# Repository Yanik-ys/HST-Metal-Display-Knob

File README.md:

# HST-Metal-Display-Knob
This repo is for the school project Metal-Display-Knob

The project is based on the project [smartknob](https://github.com/scottbez1/smartknob?tab=readme-ov-file) from [scottbez1](https://github.com/scottbez1)

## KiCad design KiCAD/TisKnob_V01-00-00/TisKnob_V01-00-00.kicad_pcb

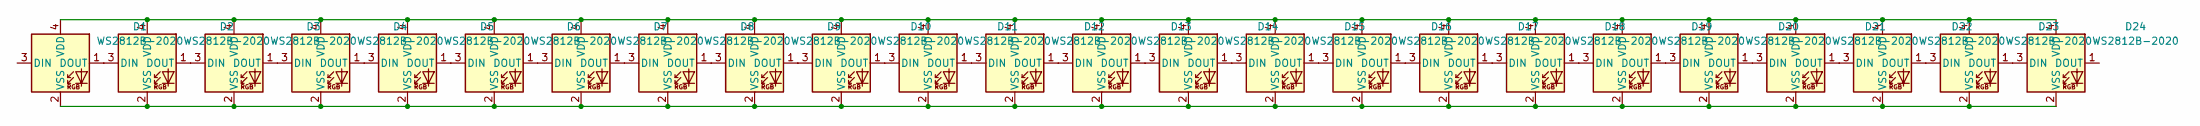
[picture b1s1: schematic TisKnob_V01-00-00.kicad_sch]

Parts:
D1, D2, D3, D4, D5, D6, D7, D8, D9, D10, D11, D12, D13, D14, D15, D16, D17, D18, D19, D20, D21, D22, D23, D24: WS2812B-2020; LED_WS2812B-2020_PLCC4_2.0x2.0mm

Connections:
unnamed: D1.1 (DOUT), D2.3 (DIN)
unnamed: D1.4 (VDD), D2.4 (VDD), D3.4 (VDD), D4.4 (VDD), D5.4 (VDD), D6.4 (VDD), D7.4 (VDD), D8.4 (VDD), D9.4 (VDD), D10.4 (VDD), D11.4 (VDD), D12.4 (VDD), D13.4 (VDD), D14.4 (VDD), D15.4 (VDD), D16.4 (VDD), D17.4 (VDD), D18.4 (VDD), D19.4 (VDD), D20.4 (VDD), D21.4 (VDD), D22.4 (VDD), D23.4 (VDD), D24.4 (VDD)
unnamed: D1.2 (VSS), D2.2 (VSS), D3.2 (VSS), D4.2 (VSS), D5.2 (VSS), D6.2 (VSS), D7.2 (VSS), D8.2 (VSS), D9.2 (VSS), D10.2 (VSS), D11.2 (VSS), D12.2 (VSS), D13.2 (VSS), D14.2 (VSS), D15.2 (VSS), D16.2 (VSS), D17.2 (VSS), D18.2 (VSS), D19.2 (VSS), D20.2 (VSS), D21.2 (VSS), D22.2 (VSS), D23.2 (VSS), D24.2 (VSS)
unnamed: D2.1 (DOUT), D3.3 (DIN)
unnamed: D3.1 (DOUT), D4.3 (DIN)
unnamed: D4.1 (DOUT), D5.3 (DIN)
unnamed: D5.1 (DOUT), D6.3 (DIN)
unnamed: D6.1 (DOUT), D7.3 (DIN)
unnamed: D7.1 (DOUT), D8.3 (DIN)
unnamed: D8.1 (DOUT), D9.3 (DIN)
unnamed: D9.1 (DOUT), D10.3 (DIN)
unnamed: D10.1 (DOUT), D11.3 (DIN)
unnamed: D11.1 (DOUT), D12.3 (DIN)
unnamed: D12.1 (DOUT), D13.3 (DIN)
unnamed: D13.1 (DOUT), D14.3 (DIN)
unnamed: D14.1 (DOUT), D15.3 (DIN)
unnamed: D15.1 (DOUT), D16.3 (DIN)
unnamed: D16.1 (DOUT), D17.3 (DIN)
unnamed: D17.1 (DOUT), D18.3 (DIN)
unnamed: D18.1 (DOUT), D19.3 (DIN)
unnamed: D19.1 (DOUT), D20.3 (DIN)
unnamed: D20.1 (DOUT), D21.3 (DIN)
unnamed: D21.1 (DOUT), D22.3 (DIN)
unnamed: D22.1 (DOUT), D23.3 (DIN)
unnamed: D23.1 (DOUT), D24.3 (DIN)

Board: 2 copper layers, 24 parts (0 on the bottom side), 25 nets, no tracks yet.

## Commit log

2026-02-06 Create README.md in CAD
    Created readme for the CAD data
2026-03-06 create Kicad
2026-03-06 Added new lib
2026-03-06 KiCAD
